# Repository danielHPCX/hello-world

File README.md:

# hello-world
tutorial

alteração

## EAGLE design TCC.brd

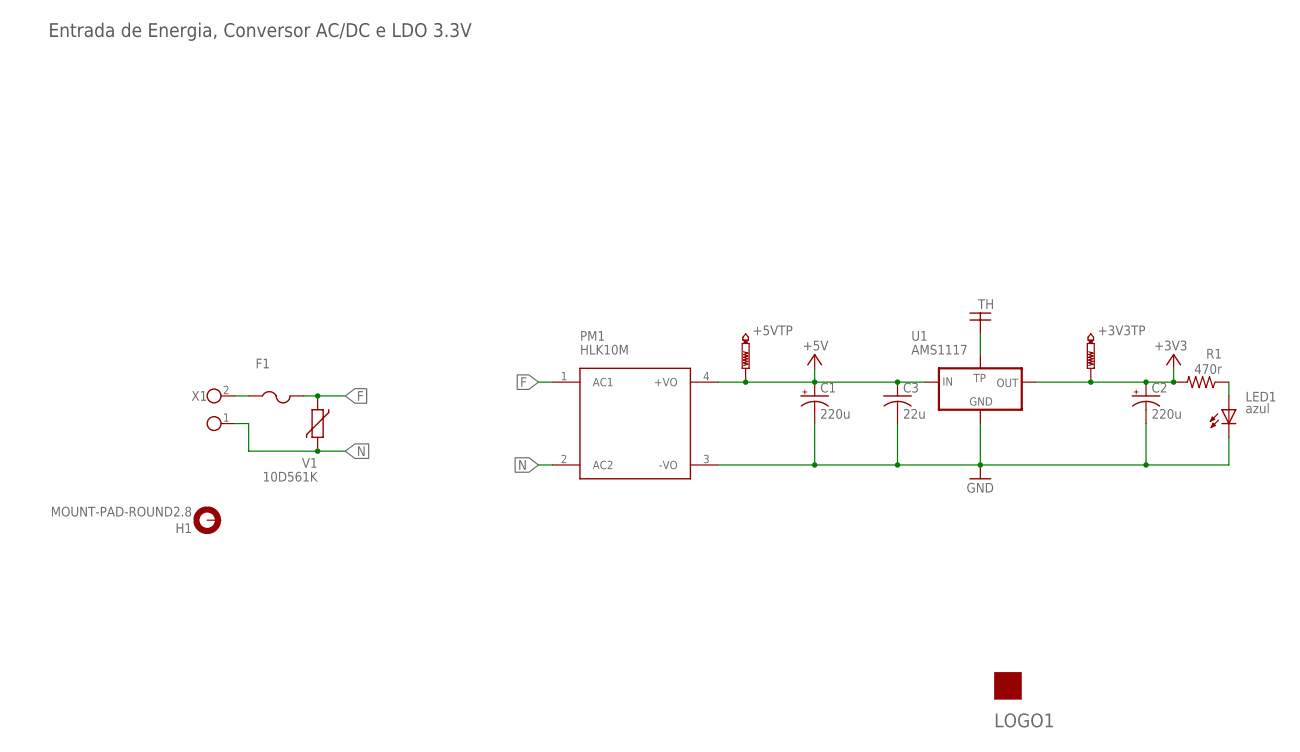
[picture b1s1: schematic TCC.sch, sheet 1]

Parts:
+3V3TP, +5VTP: PTR1TP18R; TP18R
C1, C2: 220u; E3,5-8
C3: 22u; C0805
F1: FUSE; SHK20L
H1: MOUNT-PAD-ROUND2.8; 2,8-PAD
LED1: azul; LED3MM
LOGO1: LOGOLOGO1; LOGO_BRAZIL_FLAG
PM1: HLK10M; HLK-10M
R1: 470r; R0805
U1: AMS1117; SOT223
V1: 10D561K
X1: TERM_BLOCK_2PBR1002V; BR1002V

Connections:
+3V3: +3V3TP.TP, C2.+, R1.2, U1.2 (OUT); also elsewhere on the board
+5V: +5VTP.TP, C1.+, C3.1, PM1.4 (+VO), U1.3 (IN); also elsewhere on the board
F: F1.2A (2), F1.2B (2), PM1.1 (AC1), V1.1; also elsewhere on the board
GND: C1.-, C2.-, C3.2, LED1.K (C), PM1.3 (-VO), U1.1 (GND); also elsewhere on the board
N: PM1.2 (AC2), V1.2, X1.1; also elsewhere on the board
unnamed: F1.1A (1), F1.1B (1), X1.2
unnamed: LED1.A, R1.1
TH: U1.4 (TP)

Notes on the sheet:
Entrada de Energia, Conversor AC/DC e LDO 3.3V

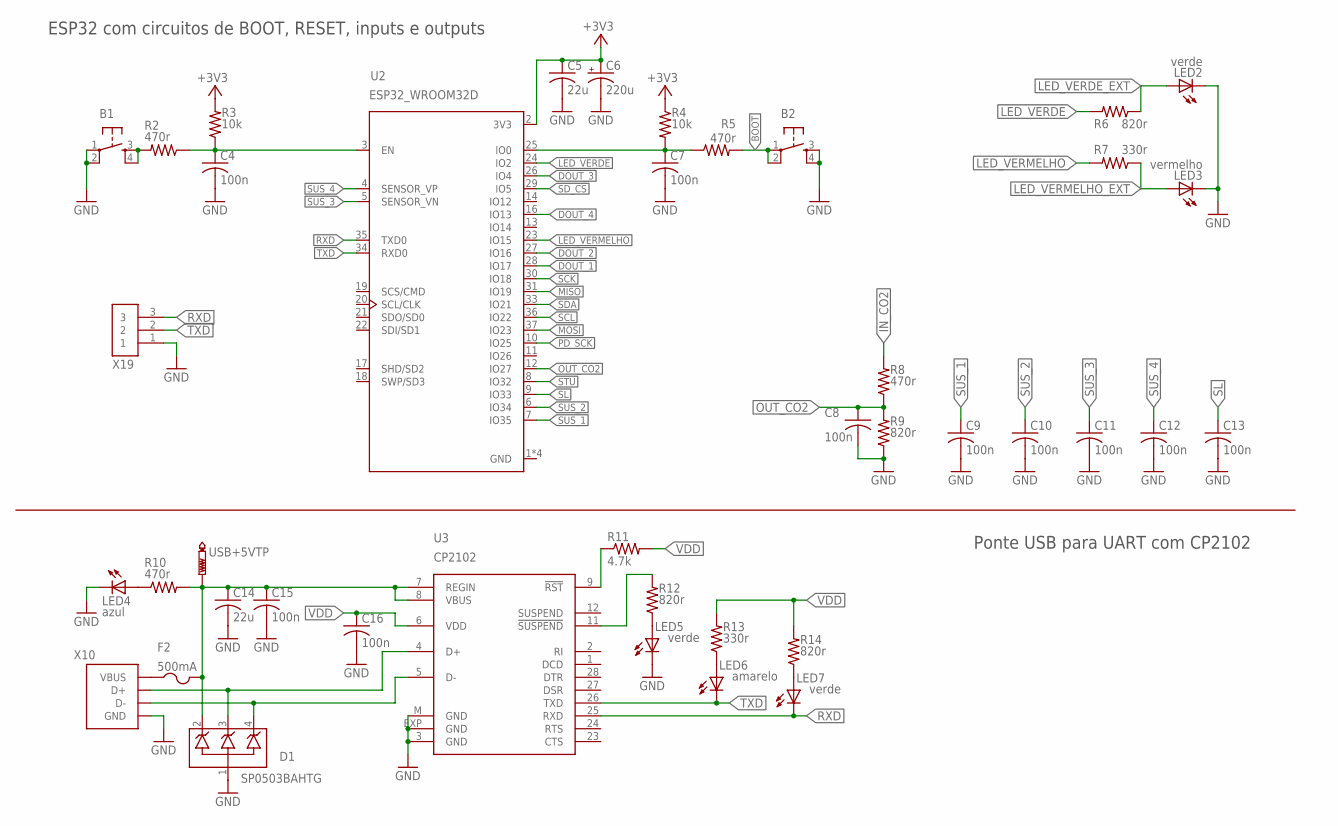
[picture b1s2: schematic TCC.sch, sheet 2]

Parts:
B1, B2: PUSHBUTTONTHT; B3F-10XX
C4, C7, C8, C9, C10, C11, C12, C13, C15, C16: 100n; C0805
C5, C14: 22u; C0805
C6: 220u; E3,5-8
D1: SP0503BAHTG; SOT-143
F2: 500mA; C0603
LED2, LED5, LED7: verde; LED3MM
LED3: vermelho; LED3MM
LED4: azul; LED3MM
LED6: amarelo; LED3MM
R2, R5, R8, R10: 470r; R0805
R3, R4: 10k; R0805
R6, R9, R12, R14: 820r; R0805
R7, R13: 330r; R0805
R11: 4.7k; R0805
U2: ESP32_WROOM32D; MODULE_ESP32-WROOM
U3: CP2102; MLP28
USB+5VTP: PTR1TP18R; TP18R
X10: USB_TYPEB_V; USB-TYPEB-V
X19: 1X3

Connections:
+3V3: C5.1, C6.+, R3.2, R4.1, U2.2 (3V3); also elsewhere on the board
BOOT: B2.1, B2.2, R5.2; also elsewhere on the board
DOUT_1: U2.28 (IO17); also elsewhere on the board
DOUT_2: U2.27 (IO16); also elsewhere on the board
DOUT_3: U2.26 (IO4); also elsewhere on the board
DOUT_4: U2.16 (IO13); also elsewhere on the board
GND: B1.1, B1.2, B2.3, B2.4, C4.2, C5.2, C6.-, C7.2, C8.2, C9.2, C10.2, C11.2, C12.2, C13.2, C14.2, C15.2, C16.2, D1.1, LED2.K (C), LED3.K (C), LED4.K (C), LED5.K (C), R9.1, U2.1 (GND), U2.15 (GND), U2.38 (GND), U2.39 (GND), U3.3 (GND), U3.EXP (GND), U3.M (GND), X10.GND, X10.GND@1 (GND), X10.GND@2 (GND), X19.1; also elsewhere on the board
IN_CO2: R8.2; also elsewhere on the board
LED_VERDE: R6.2, U2.24 (IO2)
LED_VERDE_EXT: LED2.A, R6.1; also elsewhere on the board
LED_VERMELHO: R7.2, U2.23 (IO15)
LED_VERMELHO_EXT: LED3.A, R7.1; also elsewhere on the board
MISO: U2.31 (IO19); also elsewhere on the board
MOSI: U2.37 (IO23); also elsewhere on the board
unnamed: C4.1, R2.1, R3.1, U2.3 (EN)
unnamed: B1.3, B1.4, R2.2
unnamed: C7.1, R4.2, R5.1, U2.25 (IO0)
unnamed: C14.1, C15.1, D1.2, F2.2, R10.2, U3.7 (REGIN), U3.8 (VBUS), USB+5VTP.TP
unnamed: LED4.A, R10.1
unnamed: F2.1, X10.VCC (VBUS)
unnamed: R11.1, U3.9 (!RST)
unnamed: D1.3, U3.4 (D+), X10.D+
unnamed: D1.4, U3.5 (D-), X10.D-
unnamed: LED6.A, R13.1
unnamed: LED7.A, R14.1
unnamed: LED5.A, R12.1
unnamed: R12.2, U3.11 (!SUSPEND)
OUT_CO2: C8.1, R8.1, R9.2, U2.12 (IO27)
PD_SCK: U2.10 (IO25); also elsewhere on the board
RXD: LED7.K (C), U2.35 (TXD0), U3.25 (RXD), X19.3
SCK: U2.30 (IO18); also elsewhere on the board
SCL: U2.36 (IO22); also elsewhere on the board
SDA: U2.33 (IO21); also elsewhere on the board
SD_CS: U2.29 (IO5); also elsewhere on the board
SL: C13.1, U2.9 (IO33); also elsewhere on the board
STU: U2.8 (IO32); also elsewhere on the board
SUS_1: C9.1, U2.7 (IO35); also elsewhere on the board
SUS_2: C10.1, U2.6 (IO34); also elsewhere on the board
SUS_3: C11.1, U2.5 (SENSOR_VN); also elsewhere on the board
SUS_4: C12.1, U2.4 (SENSOR_VP); also elsewhere on the board
TXD: LED6.K (C), U2.34 (RXD0), U3.26 (TXD), X19.2
VDD: C16.1, R11.2, R13.2, R14.2, U3.6 (VDD)

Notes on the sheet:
ESP32 com circuitos de BOOT, RESET, inputs e outputs
Ponte USB para UART com CP2102

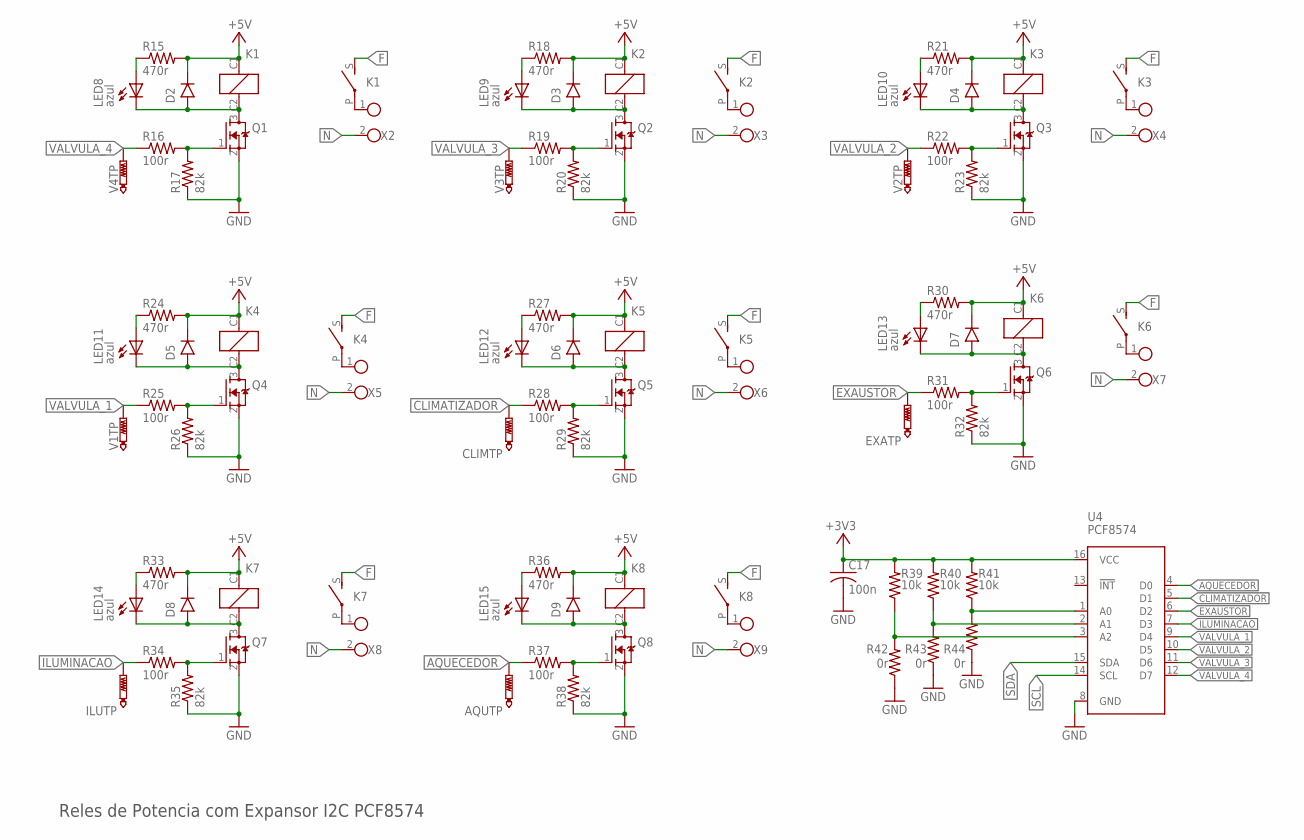
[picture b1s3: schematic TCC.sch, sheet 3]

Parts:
AQUTP: PTR1TP18R; TP18R
C17: 100n; C0805
CLIMTP: PTR1TP18R; TP18R
D2, D3, D4, D5, D6, D7, D8, D9: DIODEM7; SMA
EXATP: PTR1TP18R; TP18R
ILUTP: PTR1TP18R; TP18R
K1, K2, K3, K4, K5, K6, K7, K8: RELAY_SPST; RC-105
LED8, LED9, LED10, LED11, LED12, LED13, LED14, LED15: azul; LED3MM
Q1, Q2, Q3, Q4, Q5, Q6, Q7, Q8: MOSFET-NBSS138; SOT23
R15, R18, R21, R24, R27, R30, R33, R36: 470r; R0805
R16, R19, R22, R25, R28, R31, R34, R37: 100r; R0805
R17, R20, R23, R26, R29, R32, R35, R38: 82k; R0805
R39, R40, R41: 10k; R0805
R42, R43, R44: 0r; R0805
U4: PCF8574; SOIC16_W
V1TP, V2TP, V3TP, V4TP: PTR1TP18R; TP18R
X2, X3, X4, X5, X6, X7, X8, X9: TERM_BLOCK_2PBR1002V; BR1002V

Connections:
+3V3: C17.1, R39.2, R40.2, R41.2, U4.16 (VCC); also elsewhere on the board
+5V: D2.C, D3.C, D4.C, D5.C, D6.C, D7.C, D8.C, D9.C, K1.C1 (1), K2.C1 (1), K3.C1 (1), K4.C1 (1), K5.C1 (1), K6.C1 (1), K7.C1 (1), K8.C1 (1), R15.2, R18.2, R21.2, R24.2, R27.2, R30.2, R33.2, R36.2; also elsewhere on the board
AQUECEDOR: AQUTP.TP, R37.1, U4.4 (D0)
CLIMATIZADOR: CLIMTP.TP, R28.1, U4.5 (D1)
EXAUSTOR: EXATP.TP, R31.1, U4.6 (D2)
F: K1.S, K2.S, K3.S, K4.S, K5.S, K6.S, K7.S, K8.S; also elsewhere on the board
GND: C17.2, Q1.2 (S), Q2.2 (S), Q3.2 (S), Q4.2 (S), Q5.2 (S), Q6.2 (S), Q7.2 (S), Q8.2 (S), R17.1, R20.1, R23.1, R26.1, R29.1, R32.1, R35.1, R38.1, R42.1, R43.1, R44.1, U4.8 (GND); also elsewhere on the board
ILUMINACAO: ILUTP.TP, R34.1, U4.7 (D3)
N: X2.2, X3.2, X4.2, X5.2, X6.2, X7.2, X8.2, X9.2; also elsewhere on the board
unnamed: D2.A, K1.C2 (2), LED8.K (C), Q1.3 (D)
unnamed: LED8.A, R15.1
unnamed: Q1.1 (G), R16.2, R17.2
unnamed: K8.P, X9.1
unnamed: D3.A, K2.C2 (2), LED9.K (C), Q2.3 (D)
unnamed: Q2.1 (G), R19.2, R20.2
unnamed: LED9.A, R18.1
unnamed: K1.P, X2.1
unnamed: D4.A, K3.C2 (2), LED10.K (C), Q3.3 (D)
unnamed: Q3.1 (G), R22.2, R23.2
unnamed: LED10.A, R21.1
unnamed: K2.P, X3.1
unnamed: D5.A, K4.C2 (2), LED11.K (C), Q4.3 (D)
unnamed: Q4.1 (G), R25.2, R26.2
unnamed: LED11.A, R24.1
unnamed: K3.P, X4.1
unnamed: D6.A, K5.C2 (2), LED12.K (C), Q5.3 (D)
unnamed: Q5.1 (G), R28.2, R29.2
unnamed: LED12.A, R27.1
unnamed: K4.P, X5.1
unnamed: D7.A, K6.C2 (2), LED13.K (C), Q6.3 (D)
unnamed: Q6.1 (G), R31.2, R32.2
unnamed: LED13.A, R30.1
unnamed: K5.P, X6.1
unnamed: D8.A, K7.C2 (2), LED14.K (C), Q7.3 (D)
unnamed: Q7.1 (G), R34.2, R35.2
unnamed: LED14.A, R33.1
unnamed: K6.P, X7.1
unnamed: D9.A, K8.C2 (2), LED15.K (C), Q8.3 (D)
unnamed: Q8.1 (G), R37.2, R38.2
unnamed: LED15.A, R36.1
unnamed: K7.P, X8.1
unnamed: R41.1, R44.2, U4.1 (A0)
unnamed: R40.1, R43.2, U4.2 (A1)
unnamed: R39.1, R42.2, U4.3 (A2)
SCL: U4.14 (SCL); also elsewhere on the board
SDA: U4.15 (SDA); also elsewhere on the board
VALVULA_1: R25.1, U4.9 (D4), V1TP.TP
VALVULA_2: R22.1, U4.10 (D5), V2TP.TP
VALVULA_3: R19.1, U4.11 (D6), V3TP.TP
VALVULA_4: R16.1, U4.12 (D7), V4TP.TP

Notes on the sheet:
Reles de Potencia com Expansor I2C PCF8574

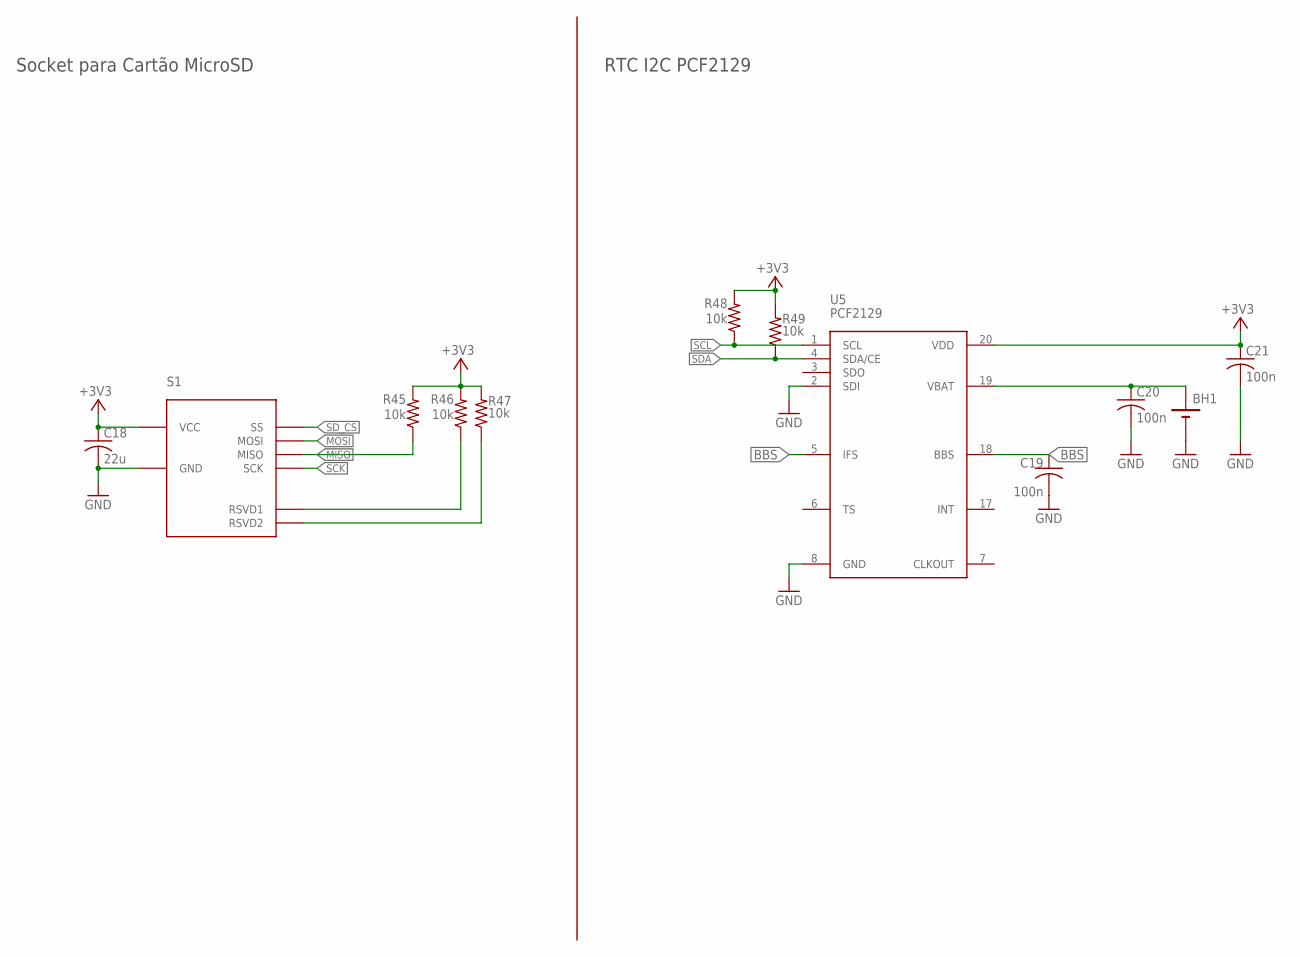
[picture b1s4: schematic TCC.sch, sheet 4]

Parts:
BH1: CR2032; BAT_BS-7
C18: 22u; C0805
C19, C20, C21: 100n; C0805
R45, R46, R47, R48, R49: 10k; R0805
S1: MICROSDSOCKETTF-002T-15; TF-002T-15
U5: PCF2129; SOIC127P1032X264-20N

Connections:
+3V3: C18.1, C21.1, R45.2, R46.2, R47.2, R48.2, R49.2, S1.VDD (VCC), U5.20 (VDD); also elsewhere on the board
BBS: C19.1, U5.5 (IFS), U5.18 (BBS)
GND: BH1.-, C18.2, C19.2, C20.2, C21.2, S1.GND, S1.PAD@1 (GND), S1.PAD@2 (GND), S1.PAD@3 (GND), S1.PAD@4 (GND), U5.2 (SDI), U5.8 (GND); also elsewhere on the board
MISO: R45.1, S1.MISO; also elsewhere on the board
MOSI: S1.MOSI; also elsewhere on the board
unnamed: R46.1, S1.RES@1 (RSVD1)
unnamed: R47.1, S1.RES@2 (RSVD2)
unnamed: BH1.+, C20.1, U5.19 (VBAT)
SCK: S1.SCK; also elsewhere on the board
SCL: R48.1, U5.1 (SCL); also elsewhere on the board
SDA: R49.1, U5.4 (SDA/CE); also elsewhere on the board
SD_CS: S1.CS (SS); also elsewhere on the board

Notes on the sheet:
Socket para Cartão MicroSD
RTC I2C PCF2129

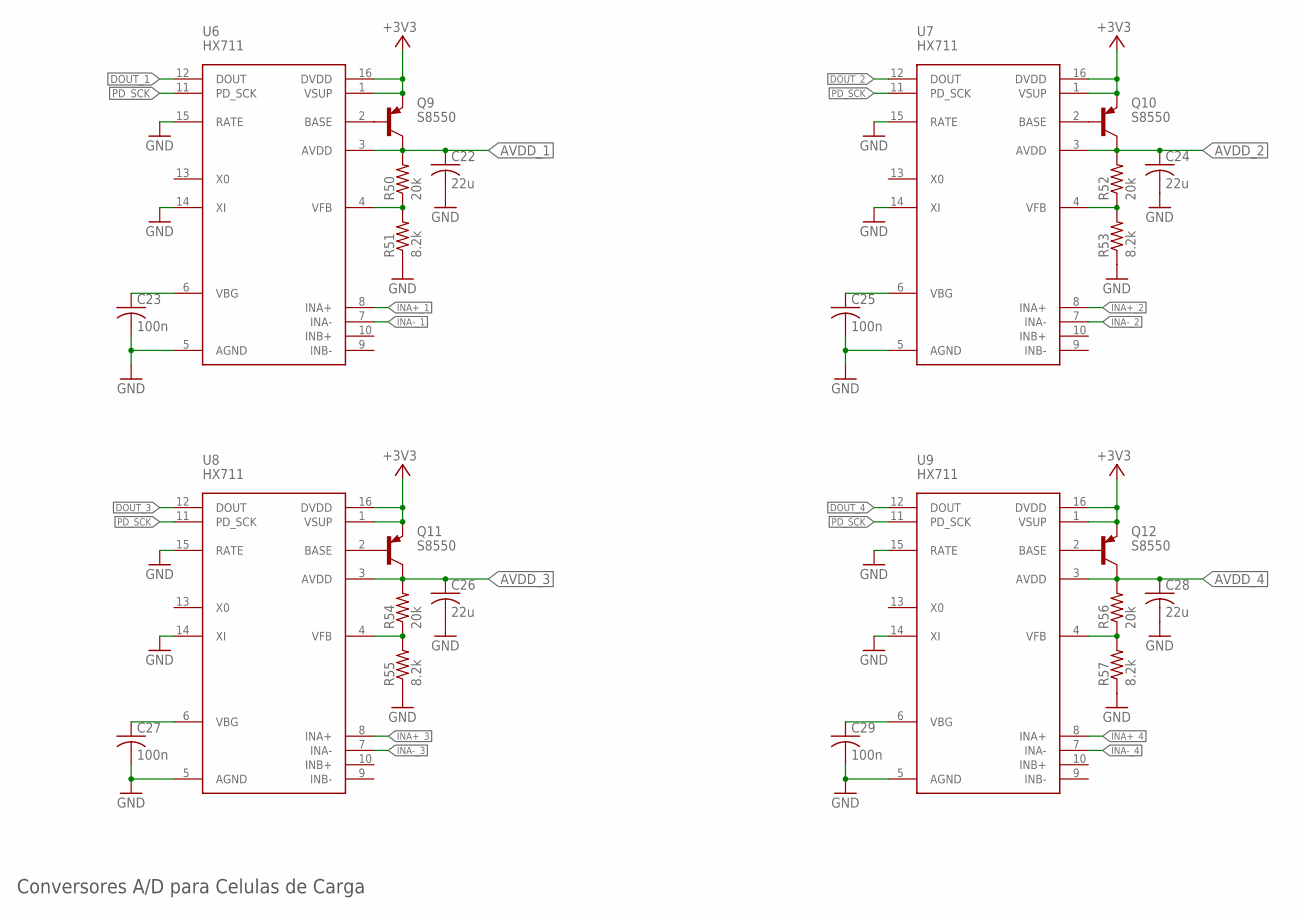
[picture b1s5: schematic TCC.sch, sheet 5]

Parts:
C22, C24, C26, C28: 22u; C0805
C23, C25, C27, C29: 100n; C0805
Q9, Q10, Q11, Q12: S8550; SOT23
R50, R52, R54, R56: 20k; R0805
R51, R53, R55, R57: 8.2k; R0805
U6, U7, U8, U9: HX711; SOP16

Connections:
+3V3: Q9.2 (E), Q10.2 (E), Q11.2 (E), Q12.2 (E), U6.1 (VSUP), U6.16 (DVDD), U7.1 (VSUP), U7.16 (DVDD), U8.1 (VSUP), U8.16 (DVDD), U9.1 (VSUP), U9.16 (DVDD); also elsewhere on the board
AVDD_1: C22.1, Q9.3 (C), R50.2, U6.3 (AVDD); also elsewhere on the board
AVDD_2: C24.1, Q10.3 (C), R52.2, U7.3 (AVDD); also elsewhere on the board
AVDD_3: C26.1, Q11.3 (C), R54.2, U8.3 (AVDD); also elsewhere on the board
AVDD_4: C28.1, Q12.3 (C), R56.2, U9.3 (AVDD); also elsewhere on the board
DOUT_1: U6.12 (DOUT); also elsewhere on the board
DOUT_2: U7.12 (DOUT); also elsewhere on the board
DOUT_3: U8.12 (DOUT); also elsewhere on the board
DOUT_4: U9.12 (DOUT); also elsewhere on the board
GND: C22.2, C23.2, C24.2, C25.2, C26.2, C27.2, C28.2, C29.2, R51.1, R53.1, R55.1, R57.1, U6.5 (AGND), U6.14 (XI), U6.15 (RATE), U7.5 (AGND), U7.14 (XI), U7.15 (RATE), U8.5 (AGND), U8.14 (XI), U8.15 (RATE), U9.5 (AGND), U9.14 (XI), U9.15 (RATE); also elsewhere on the board
INA+_1: U6.8 (INA+); also elsewhere on the board
INA+_2: U7.8 (INA+); also elsewhere on the board
INA+_3: U8.8 (INA+); also elsewhere on the board
INA+_4: U9.8 (INA+); also elsewhere on the board
INA-_1: U6.7 (INA-); also elsewhere on the board
INA-_2: U7.7 (INA-); also elsewhere on the board
INA-_3: U8.7 (INA-); also elsewhere on the board
INA-_4: U9.7 (INA-); also elsewhere on the board
unnamed: Q9.1 (B), U6.2 (BASE)
unnamed: R50.1, R51.2, U6.4 (VFB)
unnamed: Q10.1 (B), U7.2 (BASE)
unnamed: C23.1, U6.6 (VBG)
unnamed: R52.1, R53.2, U7.4 (VFB)
unnamed: C25.1, U7.6 (VBG)
unnamed: Q11.1 (B), U8.2 (BASE)
unnamed: R54.1, R55.2, U8.4 (VFB)
unnamed: C27.1, U8.6 (VBG)
unnamed: Q12.1 (B), U9.2 (BASE)
unnamed: R56.1, R57.2, U9.4 (VFB)
unnamed: C29.1, U9.6 (VBG)
PD_SCK: U6.11 (PD_SCK), U7.11 (PD_SCK), U8.11 (PD_SCK), U9.11 (PD_SCK); also elsewhere on the board

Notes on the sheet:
Conversores A/D para Celulas de Carga

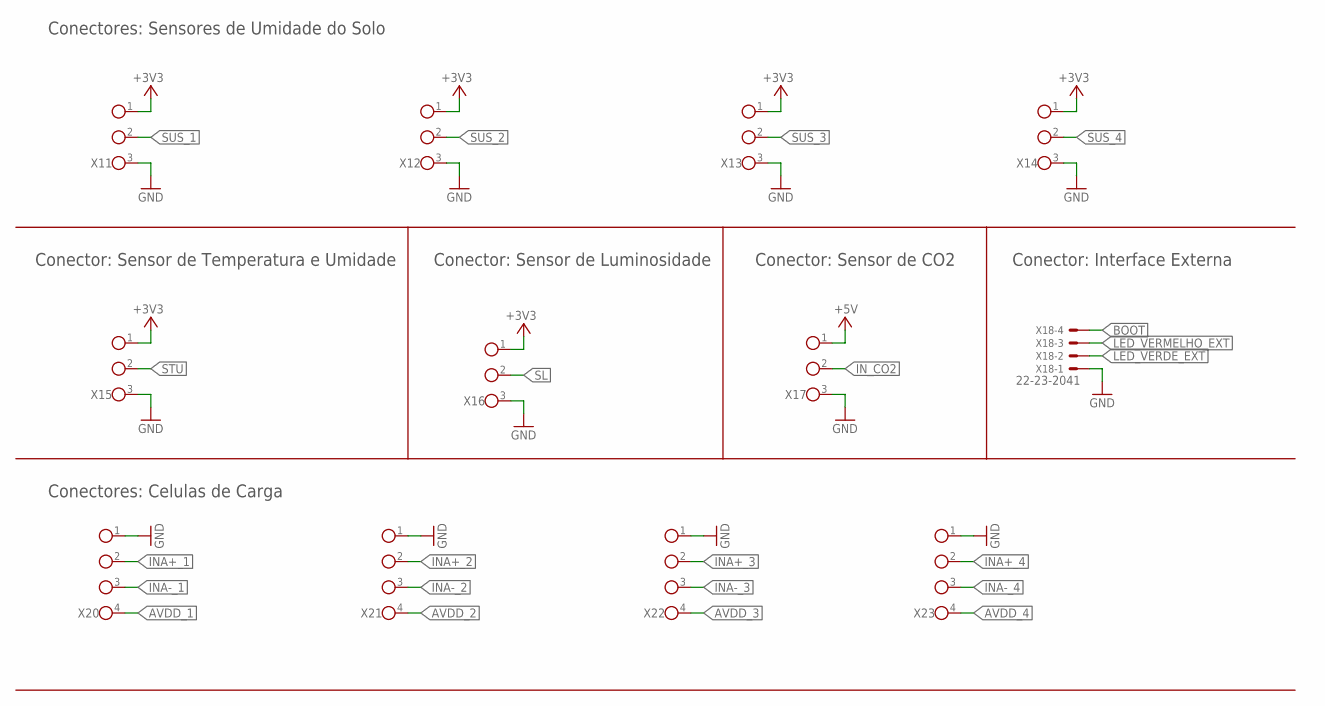
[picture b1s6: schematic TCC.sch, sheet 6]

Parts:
X11, X12, X13, X14, X15, X16, X17: TERM_BLOCK_3P; TE_1-2834011-3
X18: 22-23-2041
X20, X21, X22, X23: TERM_BLOCK_4P; TE_1-2834011-4

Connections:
+3V3: X11.1, X12.1, X13.1, X14.1, X15.1, X16.1; also elsewhere on the board
+5V: X17.1; also elsewhere on the board
AVDD_1: X20.4; also elsewhere on the board
AVDD_2: X21.4; also elsewhere on the board
AVDD_3: X22.4; also elsewhere on the board
AVDD_4: X23.4; also elsewhere on the board
BOOT: X18.4; also elsewhere on the board
GND: X11.3, X12.3, X13.3, X14.3, X15.3, X16.3, X17.3, X18.1, X20.1, X21.1, X22.1, X23.1; also elsewhere on the board
INA+_1: X20.2; also elsewhere on the board
INA+_2: X21.2; also elsewhere on the board
INA+_3: X22.2; also elsewhere on the board
INA+_4: X23.2; also elsewhere on the board
INA-_1: X20.3; also elsewhere on the board
INA-_2: X21.3; also elsewhere on the board
INA-_3: X22.3; also elsewhere on the board
INA-_4: X23.3; also elsewhere on the board
IN_CO2: X17.2; also elsewhere on the board
LED_VERDE_EXT: X18.2; also elsewhere on the board
LED_VERMELHO_EXT: X18.3; also elsewhere on the board
SL: X16.2; also elsewhere on the board
STU: X15.2; also elsewhere on the board
SUS_1: X11.2; also elsewhere on the board
SUS_2: X12.2; also elsewhere on the board
SUS_3: X13.2; also elsewhere on the board
SUS_4: X14.2; also elsewhere on the board

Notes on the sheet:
Conectores: Sensores de Umidade do Solo
Conector: Sensor de Temperatura e Umidade
Conector: Sensor de Luminosidade
Conector: Sensor de CO2
Conector: Interface Externa
Conectores: Celulas de Carga

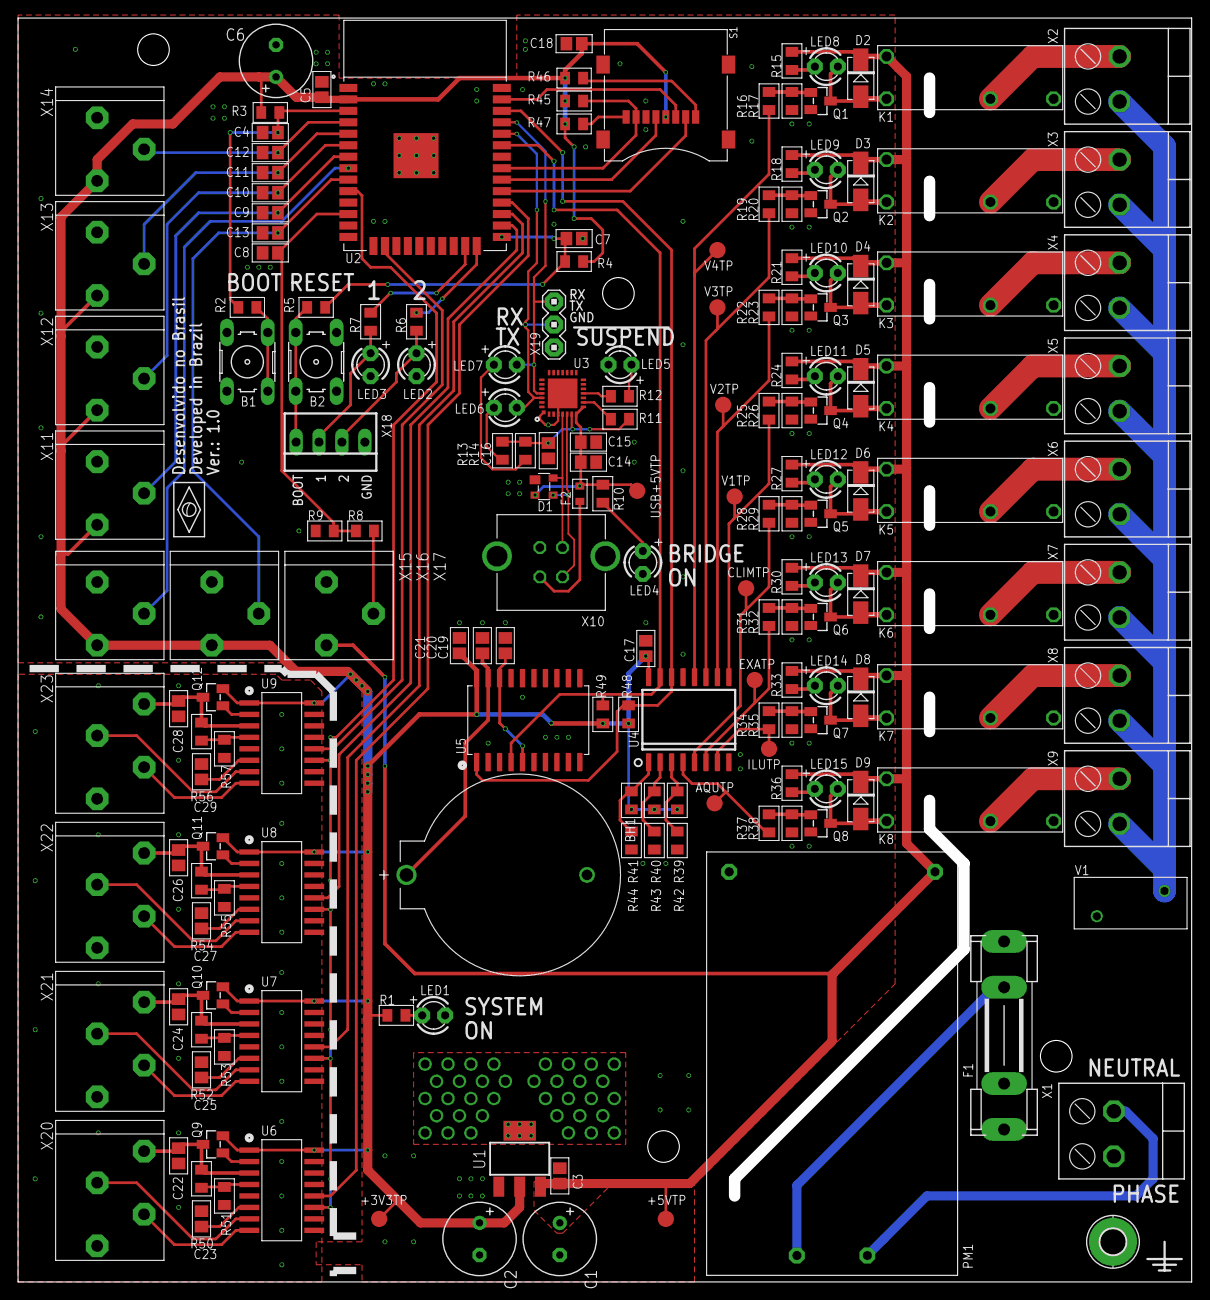
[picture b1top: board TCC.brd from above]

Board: 2 copper layers, 130.0 x 140.0 mm, 183 parts (0 on the bottom side), 118 nets.
